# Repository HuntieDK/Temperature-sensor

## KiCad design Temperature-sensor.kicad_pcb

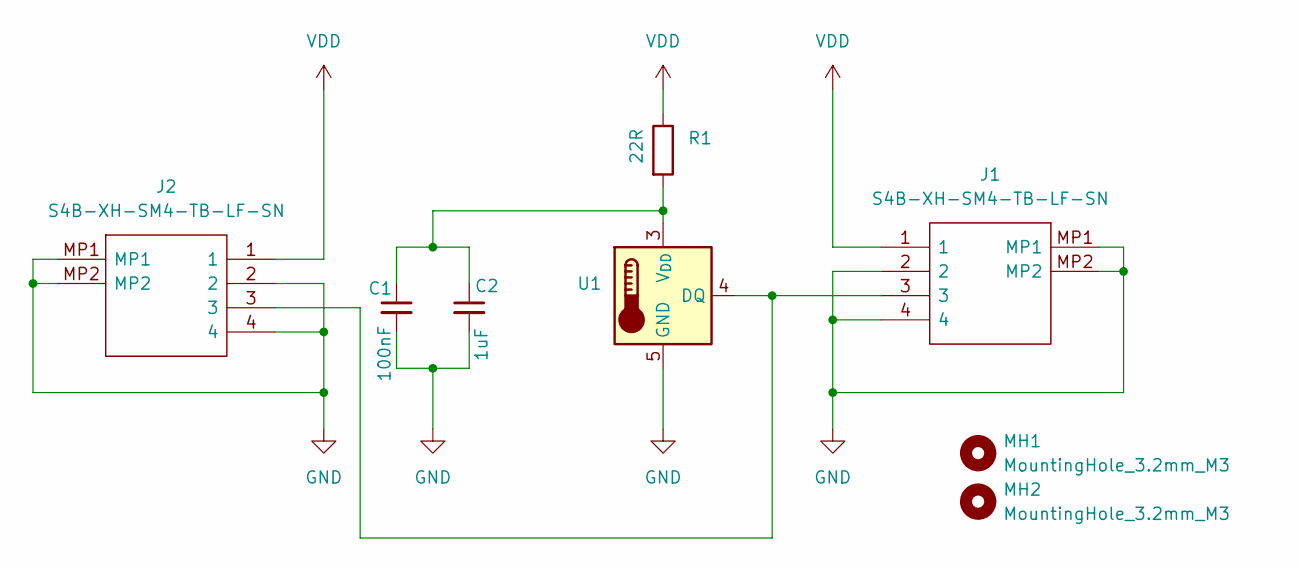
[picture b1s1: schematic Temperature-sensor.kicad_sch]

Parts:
C1: 100nF; C_0603_1608Metric; MPN CC0603KRX7R9BB104; LCSC C14663
C2: 1uF; C_0603_1608Metric; MPN CL10A105KB8NNNC; LCSC C15849
J1, J2: S4B-XH-SM4-TB-LF-SN; S4BXHSM4TBLFSN; Manufacturer_Part_Number S4B-XH-SM4-TB(LF)(SN); Mouser Part Number N/A
MH1, MH2: MountingHole_3.2mm_M3
R1: 22R; R_0603_1608Metric; MPN 0603WAF220JT5E; LCSC C23345
U1: DS18B20Z; SOIC-8_3.9x4.9mm_P1.27mm; MPN DS18B20Z(UMW); LCSC C695837

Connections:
GND: C1.2, C2.2, J1.2, J1.4, J1.MP1, J1.MP2, J2.2, J2.4, J2.MP1, J2.MP2, U1.5 (GND)
unnamed: J1.3, J2.3, U1.4 (DQ)
unnamed: C1.1, C2.1, R1.2, U1.3 (V_{DD})
VDD: J1.1, J2.1, R1.1

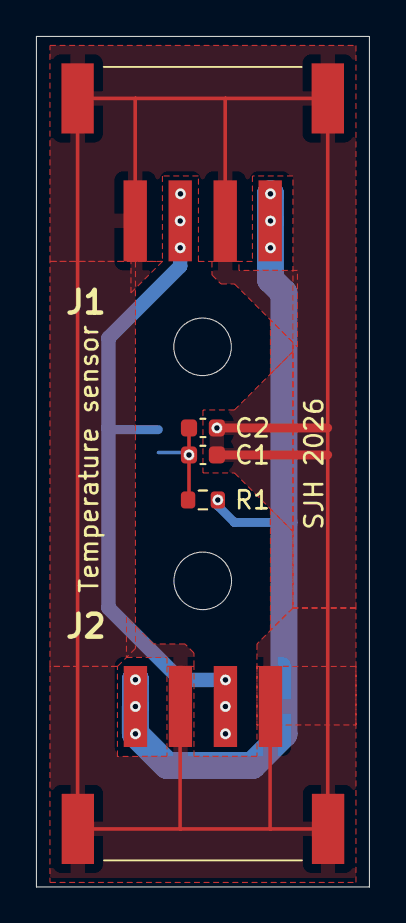
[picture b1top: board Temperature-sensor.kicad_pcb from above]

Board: 2 copper layers, 18.5 x 47.2 mm, 8 parts (1 on the bottom side), 4 nets.
